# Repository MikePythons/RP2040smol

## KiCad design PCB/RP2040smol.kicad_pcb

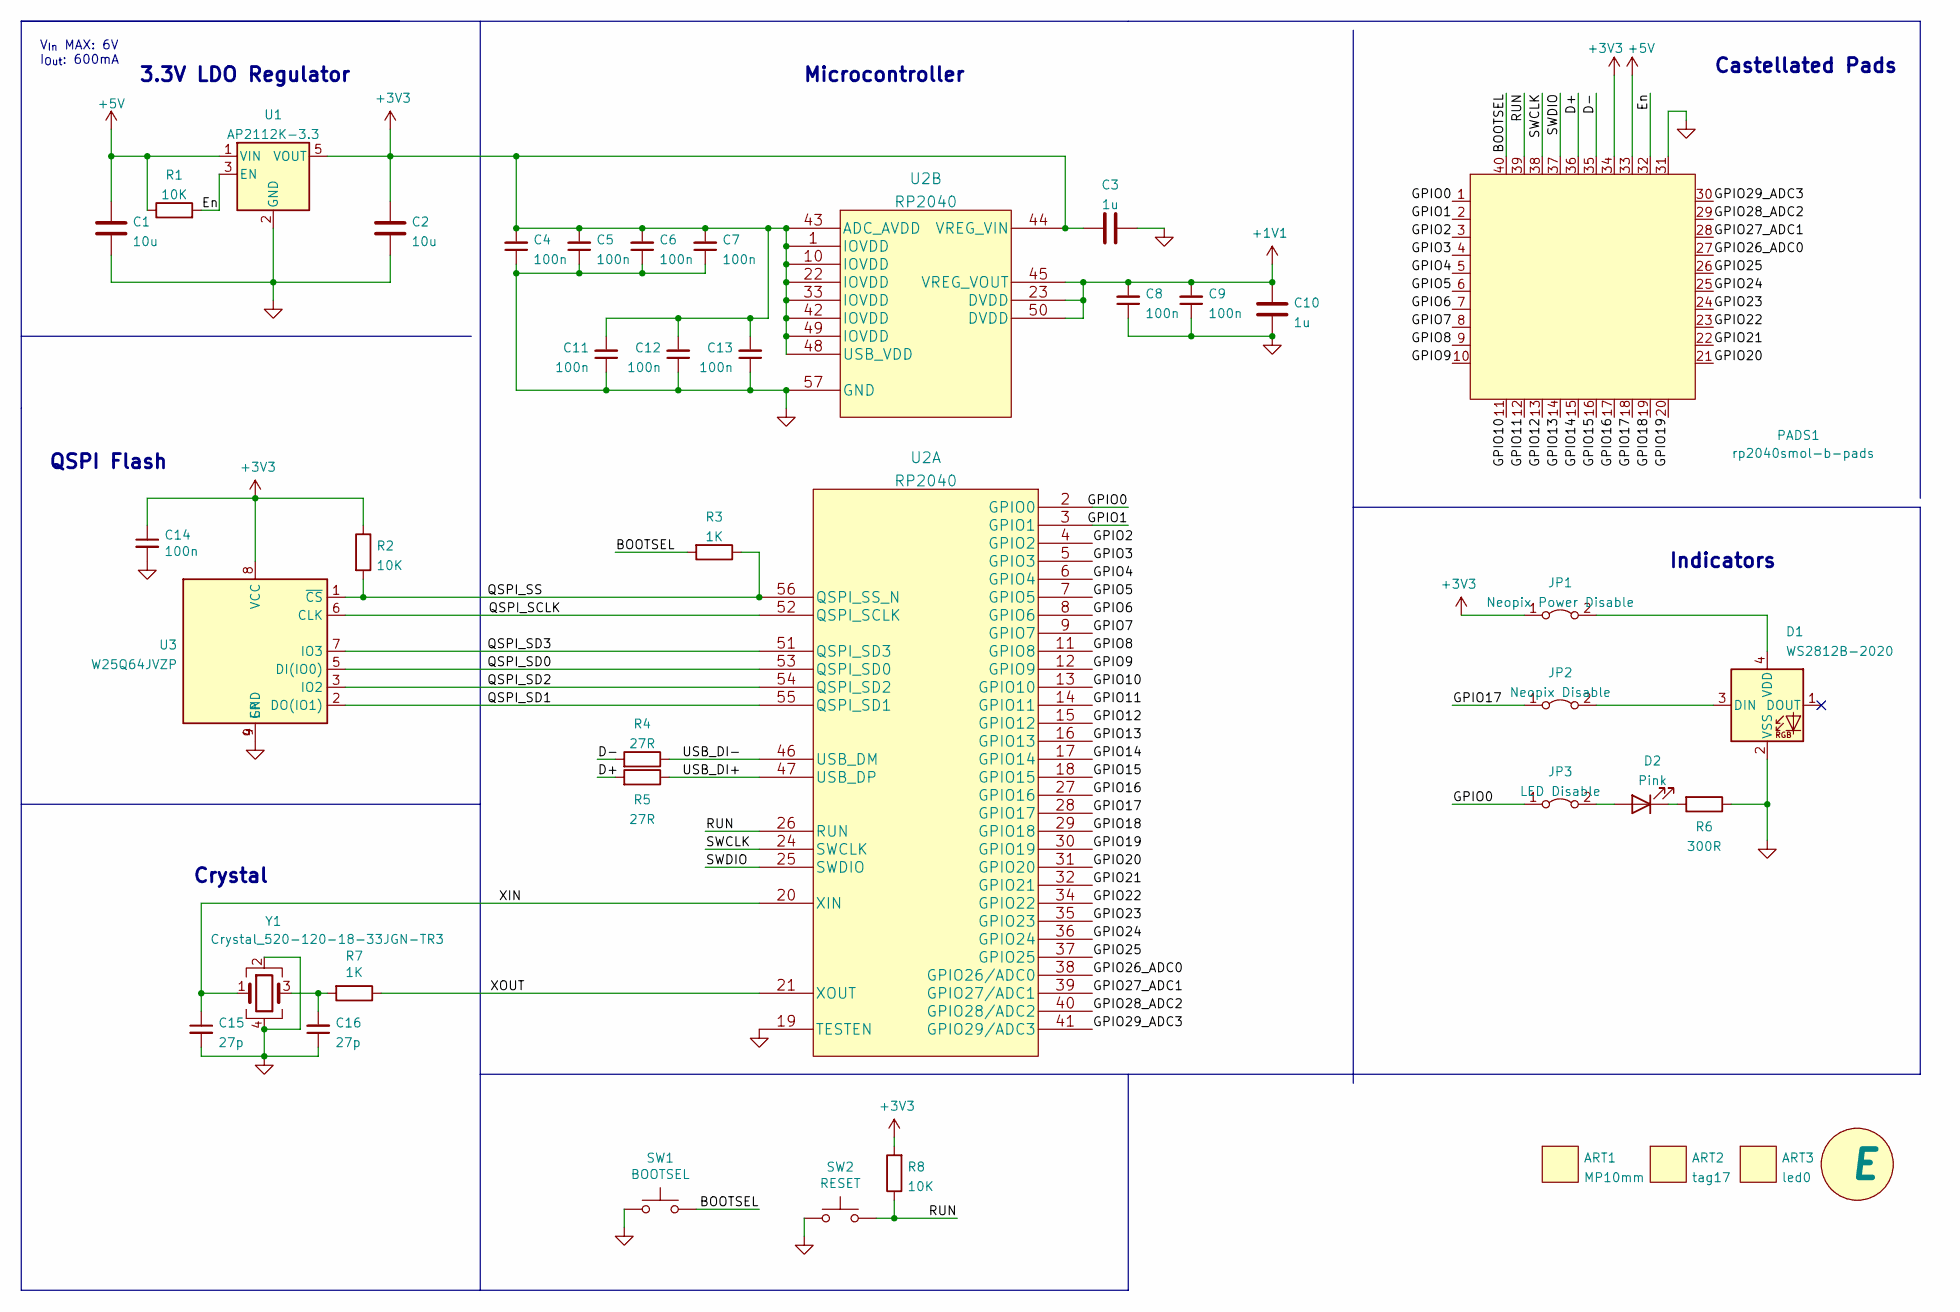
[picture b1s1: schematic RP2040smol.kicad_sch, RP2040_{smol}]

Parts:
ART1: MP10mm; MPSquare_10mm
ART2: tag17
ART3: led0; badge0
C1, C2: 10u; C_0603_1608Metric
C3, C10: 1u; C_0603_1608Metric
C4, C5, C6, C7, C8, C9, C11, C12, C13, C14: 100n; C_0603_1608Metric
C15, C16: 27p; C_0603_1608Metric
D1: WS2812B-2020; WS2812b-2020
D2: Pink; LED_0603_1608Metric
JP1: Neopix Power Disable; Covered_SolderJumper-2_P1.3mm_Bridged_RoundedPad1.0x1.5mm
JP2: Neopix Disable; Covered_SolderJumper-2_P1.3mm_Bridged_RoundedPad1.0x1.5mm
JP3: LED Disable; Covered_SolderJumper-2_P1.3mm_Bridged_RoundedPad1.0x1.5mm
MISC1: E; RevisionSymbol_Small
PADS1: rp2040smol-b-pads; Castellated_4x10_smol_dual
R1, R2, R8: 10K; R_0603_1608Metric
R3, R7: 1K; R_0603_1608Metric
R4, R5: 27R; R_0603_1608Metric
R6: 300R; R_0603_1608Metric
SW1: BOOTSEL; SW_Push_SPST_Alps_SKRK_Clone
SW2: RESET; SW_Push_SPST_Alps_SKRK_Clone
U1: AP2112K-3.3; SOT-23-5
U2: RP2040
U3: W25Q64JVZP; WSON-8-1EP_6x5mm_P1.27mm_EP3.4x4.3mm
Y1: Crystal_520-120-18-33JGN-TR3; Crystal_SMD_Abracon_ABM8G-4Pin_3.2x2.5mm

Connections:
+1V1: C8.2, C9.2, C10.2, U2.23 (DVDD), U2.45 (VREG_VOUT), U2.50 (DVDD)
+3V3: C2.1, C3.2, C4.2, C5.2, C6.2, C7.2, C11.2, C12.2, C13.2, C14.1, JP1.1 (A), PADS1.34, R2.1, R8.2, U1.5 (VOUT), U2.1 (IOVDD), U2.10 (IOVDD), U2.22 (IOVDD), U2.33 (IOVDD), U2.42 (IOVDD), U2.43 (ADC_AVDD), U2.44 (VREG_VIN), U2.48 (USB_VDD), U2.49 (IOVDD), U3.8 (VCC)
+5V: C1.1, PADS1.33, R1.1, U1.1 (VIN)
/BOOTSEL: PADS1.40, R3.2, SW1.2
/D+: PADS1.36, R5.2
/D-: PADS1.35, R4.2
/En: PADS1.32, R1.2, U1.3 (EN)
/GPIO0: JP3.1 (A), PADS1.1, U2.2 (GPIO0)
/GPIO1: PADS1.2, U2.3 (GPIO1)
/GPIO2: PADS1.3, U2.4 (GPIO2)
/GPIO3: PADS1.4, U2.5 (GPIO3)
/GPIO4: PADS1.5, U2.6 (GPIO4)
/GPIO5: PADS1.6, U2.7 (GPIO5)
/GPIO6: PADS1.7, U2.8 (GPIO6)
/GPIO7: PADS1.8, U2.9 (GPIO7)
/GPIO8: PADS1.9, U2.11 (GPIO8)
/GPIO9: PADS1.10, U2.12 (GPIO9)
/GPIO10: PADS1.11, U2.13 (GPIO10)
/GPIO11: PADS1.12, U2.14 (GPIO11)
/GPIO12: PADS1.13, U2.15 (GPIO12)
/GPIO13: PADS1.14, U2.16 (GPIO13)
/GPIO14: PADS1.15, U2.17 (GPIO14)
/GPIO15: PADS1.16, U2.18 (GPIO15)
/GPIO16: PADS1.17, U2.27 (GPIO16)
/GPIO17: JP2.1 (A), PADS1.18, U2.28 (GPIO17)
/GPIO18: PADS1.19, U2.29 (GPIO18)
/GPIO19: PADS1.20, U2.30 (GPIO19)
/GPIO20: PADS1.21, U2.31 (GPIO20)
/GPIO21: PADS1.22, U2.32 (GPIO21)
/GPIO22: PADS1.23, U2.34 (GPIO22)
/GPIO23: PADS1.24, U2.35 (GPIO23)
/GPIO24: PADS1.25, U2.36 (GPIO24)
/GPIO25: PADS1.26, U2.37 (GPIO25)
/GPIO26_ADC0: PADS1.27, U2.38 (GPIO26/ADC0)
/GPIO27_ADC1: PADS1.28, U2.39 (GPIO27/ADC1)
/GPIO28_ADC2: PADS1.29, U2.40 (GPIO28/ADC2)
/GPIO29_ADC3: PADS1.30, U2.41 (GPIO29/ADC3)
/QSPI_SCLK: U2.52 (QSPI_SCLK), U3.6 (CLK)
/QSPI_SD0: U2.53 (QSPI_SD0), U3.5 (DI(IO0))
/QSPI_SD1: U2.55 (QSPI_SD1), U3.2 (DO(IO1))
/QSPI_SD2: U2.54 (QSPI_SD2), U3.3 (IO2)
/QSPI_SD3: U2.51 (QSPI_SD3), U3.7 (IO3)
/QSPI_SS: R2.2, R3.1, U2.56 (QSPI_SS_N), U3.1 (~CS)
/RUN: PADS1.39, R8.1, SW2.2, U2.26 (RUN)
/SWCLK: PADS1.38, U2.24 (SWCLK)
/SWDIO: PADS1.37, U2.25 (SWDIO)
/USB_DI+: R5.1, U2.47 (USB_DP)
/USB_DI-: R4.1, U2.46 (USB_DM)
/XIN: C15.1, U2.20 (XIN), Y1.1
/XOUT: R7.1, U2.21 (XOUT)
GND: C1.2, C2.2, C3.1, C4.1, C5.1, C6.1, C7.1, C8.1, C9.1, C10.1, C11.1, C12.1, C13.1, C14.2, C15.2, C16.1, D1.2 (VSS), PADS1.31, R6.1, SW1.1, SW2.1, U1.2 (GND), U2.19 (TESTEN), U2.57 (GND), U3.4 (GND), U3.9 (EP), Y1.2, Y1.4
unnamed: C16.2, R7.2, Y1.3
unnamed: D1.3 (DIN), JP2.2 (B)
unnamed: D1.4 (VDD), JP1.2 (B)
unnamed: D2.1 (K), R6.2
unnamed: D2.2 (A), JP3.2 (B)

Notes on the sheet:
Castellated Pads
QSPI Flash
Crystal
Microcontroller
3.3V LDO Regulator
V_{In} MAX: 6V I_{Out}: 600mA
Indicators

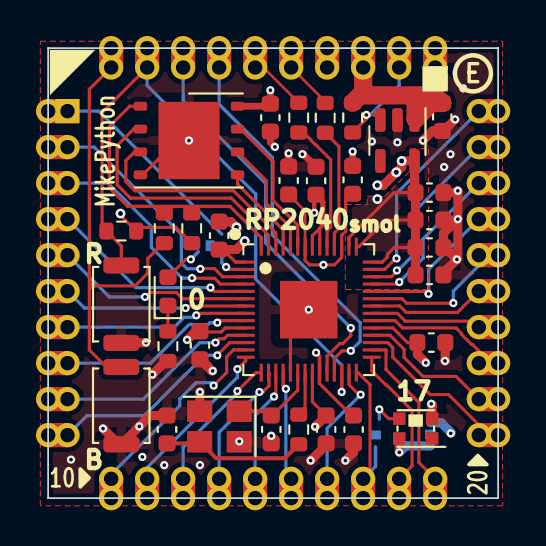
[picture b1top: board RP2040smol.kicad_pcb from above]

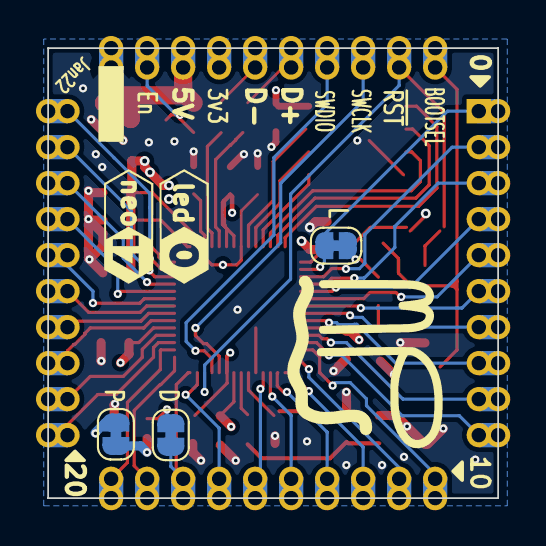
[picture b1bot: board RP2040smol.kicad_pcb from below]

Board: 4 copper layers, 25.0 x 25.0 mm, 40 parts (6 on the bottom side), 56 nets.

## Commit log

2021-12-17 Design files
2021-12-22 RevD.
    * All small passives are now 0603+
    * Pads for RP2040 and MIC5528 have been extended to try to make soldering more reasonable
    * Removed WS2812b capacitor. Hopefully the board has enough capacitance without it.
    * Rearranged BOOTSEL and Reset buttons
2022-01-07 HTML BoM fix - no physical board changes. * Set solder jumpers and castellated pads on schematic to "Exclude from BOM" * Generated RevD BoM HTML
2022-01-07 * Major schematic tidy * Changed LDO to SOT23-5 AP2112K-3.3
2022-01-08 Squeezed the bigger LDO onto the board...
2022-01-14 Tidied front silks
2022-01-14 3v3 vias
